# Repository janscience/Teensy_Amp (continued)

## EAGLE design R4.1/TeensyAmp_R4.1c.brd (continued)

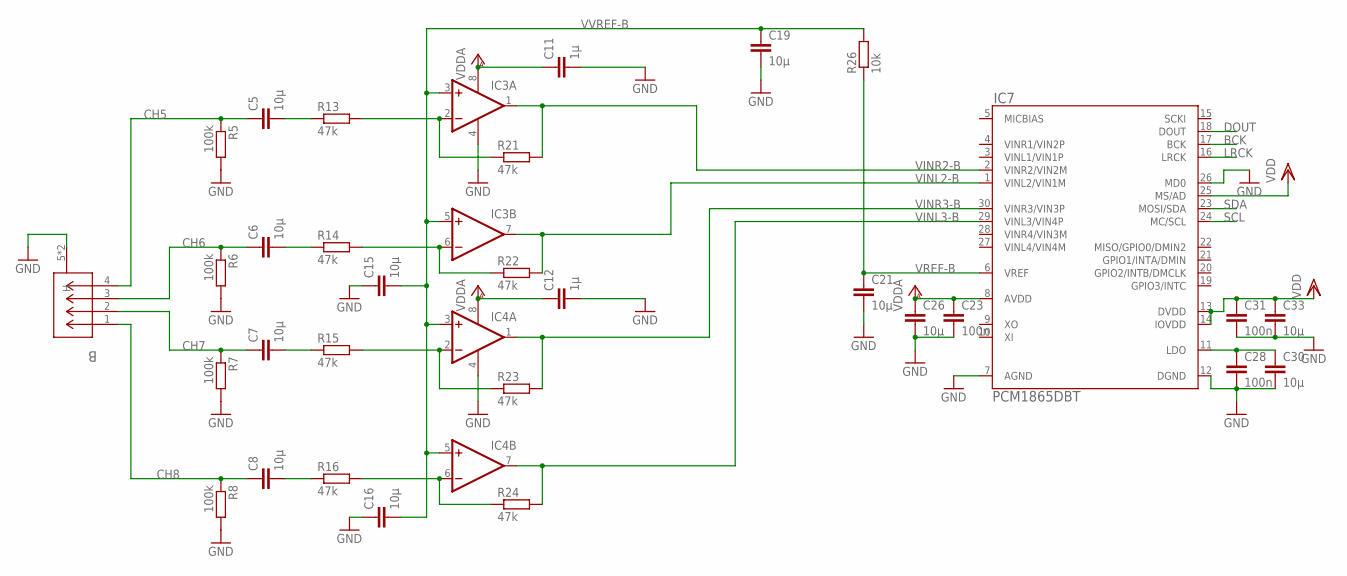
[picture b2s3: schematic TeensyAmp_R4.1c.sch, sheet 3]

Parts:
B: 5055670471; CONN04_5055670471_MOL
C5, C6, C7, C8: 10µ; C0805
C11, C12: 1µ; C0603
C15, C16, C19, C21, C26, C30, C33: 10µ; C0603
C23, C28, C31: 100n; C0603
IC3, IC4: OPA2344E; MSOP08
IC7: PCM1865DBT; SOP50P640X120-30N
R5, R6, R7, R8: 100k; R0603
R13, R14, R15, R16, R21, R22, R23, R24: 47k; R0603
R26: 10k; R0603

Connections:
BCK: IC7.17 (BCK); also elsewhere on the board
CH5: B.4, C5.1, R5.1
CH6: B.3, C6.1, R6.1
CH7: B.2, C7.1, R7.1
CH8: B.1, C8.1, R8.1
DOUT: IC7.18 (DOUT); also elsewhere on the board
GND: B.5 (H), B.6 (H), C11.2, C12.2, C15.1, C16.1, C19.2, C21.2, C23.2, C26.2, C28.2, C30.2, C31.2, C33.2, IC3.4 (V-), IC4.4 (V-), IC7.7 (AGND), IC7.12 (DGND), IC7.26 (MD0), R5.2, R6.2, R7.2, R8.2; also elsewhere on the board
LRCK: IC7.16 (LRCK); also elsewhere on the board
unnamed: C28.1, C30.1, IC7.11 (LDO)
unnamed: IC3.2 (-IN), R13.2, R21.1
unnamed: IC3.6 (-IN), R14.2, R22.1
unnamed: IC4.2 (-IN), R15.2, R23.1
unnamed: IC4.6 (-IN), R16.2, R24.1
unnamed: C6.2, R14.1
unnamed: C7.2, R15.1
unnamed: C8.2, R16.1
unnamed: C5.2, R13.1
SCL: IC7.24 (MC/SCL); also elsewhere on the board
SDA: IC7.23 (MOSI/SDA); also elsewhere on the board
VDD: C31.1, C33.1, IC7.13 (DVDD), IC7.14 (IOVDD), IC7.25 (MS/AD); also elsewhere on the board
VDDA: C11.1, C12.1, C23.1, C26.1, IC3.8 (V+), IC4.8 (V+), IC7.8 (AVDD); also elsewhere on the board
VINL2-B: IC3.7 (OUT), IC7.1 (VINL2/VIN1M), R22.2
VINL3-B: IC4.7 (OUT), IC7.29 (VINL3/VIN4P), R24.2
VINR2-B: IC3.1 (OUT), IC7.2 (VINR2/VIN2M), R21.2
VINR3-B: IC4.1 (OUT), IC7.30 (VINR3/VIN3P), R23.2
VREF-B: C21.1, IC7.6 (VREF), R26.1
VVREF-B: C15.2, C16.2, C19.1, IC3.3 (+IN), IC3.5 (+IN), IC4.3 (+IN), IC4.5 (+IN), R26.2

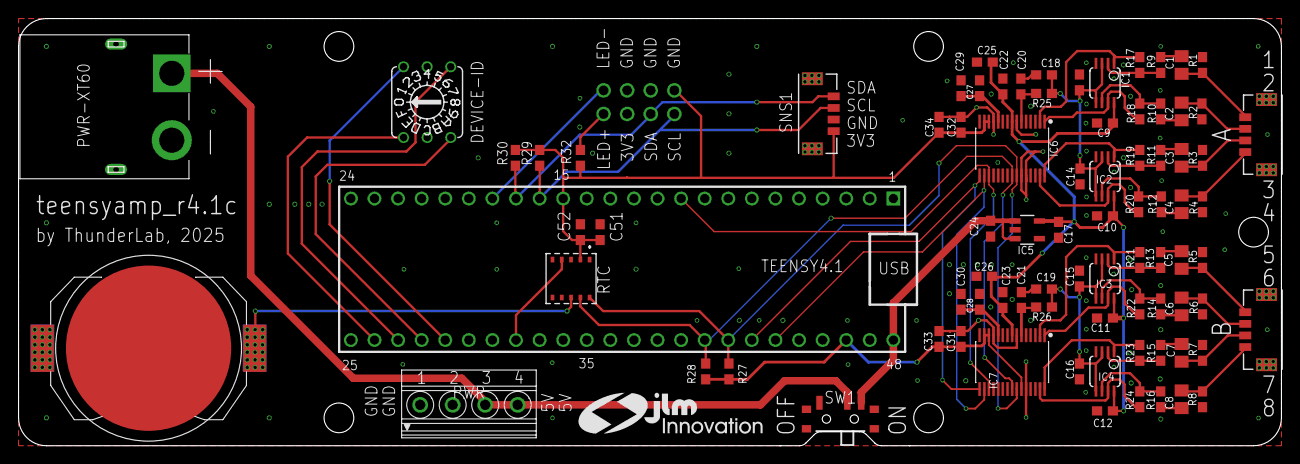
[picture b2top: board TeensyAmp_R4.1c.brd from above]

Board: 2 copper layers, 136.0 x 46.0 mm, 86 parts (0 on the bottom side), 58 nets.

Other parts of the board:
U$1: JLM_LOGO_MID

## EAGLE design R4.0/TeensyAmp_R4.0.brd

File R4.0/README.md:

# TeensyAmp R4.0

Based on
- 2 [TI PCM1865](pcm1865.md) with ADC and adjustable gain,
- [TI OPA1662](opa1662.pdf) as inverting pre-amplifier,
- [TI TCAN330](tcan334.pdf) CAN transceiver for synchronization.

by [jlm Innovation](https://www.jlm-innovation.de/) and [Jan
Benda](https://github.com/janscience).

## Circuit

- [EAGLE schematics file](TeensyAmp_R4.0.sch)
- [EAGLE circuit board](TeensyAmp_R4.0.brd)

## Pins

| Teensy 4.1 pin |              |
| -------------: | :----------- |
| Vin            | Vin          |
| GND            | GND          |
| 3.3V           | IOVDD        |
| 18             | I2C SDA      |
| 19             | I2C SCL      |
| 21             | BCK          |
| 20             | LRCK         |
| 8              | DOUT         |
| 28             | GPIO2 chip1  |
| 35             | GPIO2 chip2  |
| 29             | GPIO1 chip1  |
| 36             | GPIO1 chip2  |
| 6              | GPIO0 chip1  |
| 32             | GPIO0 chip2  |
| 0              | CAN RX       |
| 1              | CAN TX       |
| 24             | I/O In       |
| 25             | I/O Out      |
| 30             | Push button  |
| 31             | LED inverted |

### 8 input channels

The two [TI PCM1865](https://www.ti.com/product/PCM1865) together
provide 8 input channels.

You can choose between input channel that are attached to a
pre-amplifier with gain x10, or input channels without pre-amplifier
that receive the input directly via a passive high- and low-pass
filter.

| channel | PCM1865 pins with pre-amplifier | PCM1865 pins without pre-amplifier |
| ------: | :------------------------------ | :--------------------------------- |
| 0       | 1-CH1R                          | 1-CH3R                             |
| 1       | 1-CH1L                          | 1-CH3L                             |
| 2       | 1-CH2R                          | 1-CH4R                             |
| 3       | 1-CH2L                          | 1-CH4L                             |
| 4       | 2-CH1R                          | 2-CH3R                             |
| 5       | 2-CH1L                          | 2-CH3L                             |
| 6       | 2-CH2R                          | 2-CH4R                             |
| 7       | 2-CH2L                          | 2-CH4L                             |

In the following plot a 1kHz signal was supplied to each input channel in turn:

### Pre-amplifier

Inspired by
- http://realhdaudio.de/wp-content/uploads/2018/12/A0_HSD_TMT2018_realHDaudio_V3.pdf
- https://www.akm.com/content/dam/documents/products/audio/audio-adc/ak5397eq/ak5397eq-en-datasheet.pdf
- Figure 61 of the [PCM186x data sheet](https://www.ti.com/lit/gpn/pcm1865).

For variants of the pre-amplifier see [Testing filter and gain
variants](variants1.md) and [Testing high-pass filter without
low-pass](variants2.md).

#### Noise

All input channels short-circuited to ground.

- 0dB gain:

- 20dB gain:

- 40dB gain:

- No SD write artifacts.
- Super low 1-bit noise at 0dB gain.
- Noise increases accordingly with gain of the PCM chip.

#### Linearity

For the spectra, the sinewave stimuli have been applied to each
channel individually.

- 0dB gain, 150mV or 70mV rms sine wave:

- 20dB gain, 7mV rms sine wave:

- 40dB gain, 700uV rms sine wave:

- In all conditions harmonics are about 100dB below the signal!
- Noise increases according to gain (every x10 by 20dB).

#### Filter

Frequencies 10Hz to 20kHz in 1/3 octaves, each for 500ms on channel 0:

- 5Hz highpass filter

### Signal-filter (without pre-amplifier)

See figure 61 of the [PCM186x data sheet](https://www.ti.com/lit/gpn/pcm1865).

For variants of the signal filter see [Testing filter and gain
variants](variants1.md) and [Testing high-pass filter without
low-pass](variants2.md).

### Reference voltage

## CAN bus

You need to terminate both ends with a 120Ohm resistance.

## Power consumption

Teensy 4.1 on R4.0 board:

| V    | rate  | CPU    | I     | P    |
| ---- | ----- | ------ | ----- | ---- |
| 5V   | 96kHz | 600MHz | 300mA | 1.5W |
| 5V   | 96kHz | 450MHz | 270mA | 1.3W |
| 5V   | 96kHz | 150MHz | 240mA | 1.2W |
| 5V   | 96kHz |  24MHz |       |      |
| 5V   | 48kHz | 600MHz | 280mA | 1.4W |
| 5V   | 48kHz | 450MHz | 260mA | 1.3W |
| 5V   | 48kHz | 150MHz | 220mA | 1.1W |
| 5V   | 48kHz |  24MHz |       |      |
| 3.7V | 96kHz | 600MHz | 300mA | 1.1W |
| 3.7V | 96kHz | 450MHz | 270mA | 1.0W |
| 3.7V | 96kHz | 150MHz | 240mA | 0.9W |
| 3.7V | 96kHz |  24MHz |       |      |
| 3.7V | 48kHz | 600MHz | 280mA | 1.0W |
| 3.7V | 48kHz | 450MHz | 260mA | 0.9W |
| 3.7V | 48kHz | 150MHz | 220mA | 0.8W |
| 3.7V | 48kHz |  24MHz |       |      |

Underclocking works! But power savings are small.

Teensy 4.1 *without* R4.0 board:

| V    | rate  | CPU    | I     | P    |
| ---- | ----- | ------ | ----- | ---- |
| 5V   | 96kHz | 600MHz | 180mA | 0.9W |
| 5V   | 48kHz | 600MHz | 180mA | 0.9W |
| 5V   | 96kHz | 150MHz | 120mA | 0.6W |
| 5V   | 48kHz | 150MHz | 120mA | 0.6W |

The R4.0 board draws about 100mA of power.

## Battery life times

8 channel variant assumes 220mA consumption of Teensy and R4.0 amplifier board.

64 channel variant assumes 2A consumption (8x220mA consumption of Teensy and R4.0 amplifier board plus 240mA of control Teensy).

Power banks (5V):

| Capacity | 8 channels | 64 channels |
| -------- | ---------- | ----------- |
|  5Ah     |        22h |          2h |
| 10Ah     |        45h |          5h |
| 20Ah     |        90h |         10h |

Car battery (12V):

| Capacity | 8 channels | 64 channels |
| -------- | ---------- | ----------- |
| 10Ah     |       109h |         12h |
| 20Ah     |       218h |         24h |
| 40Ah     |       436h |         48h |

## Storage

For selecting appropriate SD cards, depending on sampling rates and
channels, see [data
rates](https://github.com/janscience/TeeRec/blob/main/docs/datarates.md).

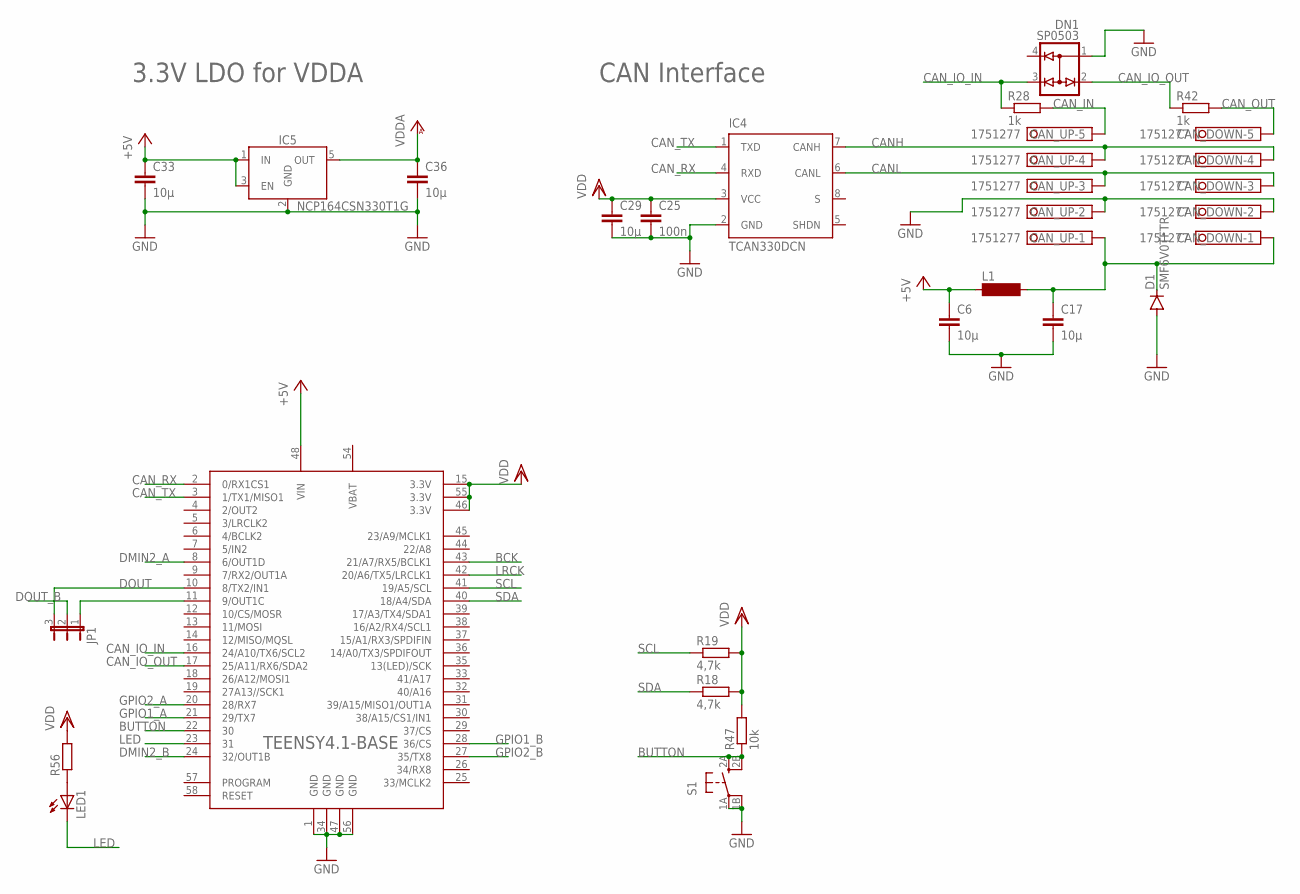
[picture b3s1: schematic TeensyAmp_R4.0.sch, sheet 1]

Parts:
C6, C17: 10µ; C0805
C25: 100n; 0402-N
C29, C33, C36: 10µ; C0603
CAN_DOWN: 1751277
CAN_UP: 1751277
D1: SMF6V0TFTR; SOD123
DN1: SP0503; SOT143-R
IC4: TCAN330DCN; SOT65P280X145-8N
IC5: NCP164CSN330T1G; SOT23-5
JP1: JP2E; JP2
L1: L_JLM0805; R0805
LED1: LEDCHIP-LED0603; CHIP-LED0603
R18, R19: 4,7k; R0402
R28, R42: 1k; 0402-N
R47: 10k; R0402
R56: R_JLMR0402; R0402
S1: SWITCH7914; 7914J
TEENSY4.1: TEENSY4.1

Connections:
+5V: C6.1, C33.1, IC5.1 (IN), IC5.3 (EN), L1.1, TEENSY4.1.48 (VIN)
BCK: TEENSY4.1.43 (21/A7/RX5/BCLK1); also elsewhere on the board
BUTTON: R47.1, S1.2A (S), S1.2B (S1), TEENSY4.1.22 (30)
CANH: CAN_DOWN.4, CAN_UP.4, IC4.7 (CANH)
CANL: CAN_DOWN.3, CAN_UP.3, IC4.6 (CANL)
CAN_IN: CAN_UP.5, R28.2
CAN_IO_IN: DN1.3 (C3), R28.1, TEENSY4.1.16 (24/A10/TX6/SCL2)
CAN_IO_OUT: DN1.2 (C2), R42.1, TEENSY4.1.17 (25/A11/RX6/SDA2)
CAN_OUT: CAN_DOWN.5, R42.2
CAN_RX: IC4.4 (RXD), TEENSY4.1.2 (0/RX1CS1)
CAN_TX: IC4.1 (TXD), TEENSY4.1.3 (1/TX1/MISO1)
DMIN2_A: TEENSY4.1.8 (6/OUT1D); also elsewhere on the board
DMIN2_B: TEENSY4.1.24 (32/OUT1B); also elsewhere on the board
DOUT: JP1.3, TEENSY4.1.10 (8/TX2/IN1); also elsewhere on the board
DOUT_B: JP1.2; also elsewhere on the board
GND: C6.2, C17.2, C25.2, C29.2, C33.2, C36.2, CAN_DOWN.2, CAN_UP.2, D1.A, DN1.1 (A1), IC4.2 (GND), IC5.2 (GND), S1.1A, S1.1B (P1), TEENSY4.1.1 (GND), TEENSY4.1.34 (GND), TEENSY4.1.47 (GND), TEENSY4.1.56 (GND); also elsewhere on the board
GPIO1_A: TEENSY4.1.21 (29/TX7); also elsewhere on the board
GPIO1_B: TEENSY4.1.28 (36/CS); also elsewhere on the board
GPIO2_A: TEENSY4.1.20 (28/RX7); also elsewhere on the board
GPIO2_B: TEENSY4.1.27 (35/TX8); also elsewhere on the board
LED: LED1.C, TEENSY4.1.23 (31)
LRCK: TEENSY4.1.42 (20/A6/TX5/LRCLK1); also elsewhere on the board
unnamed: C17.1, CAN_DOWN.1, CAN_UP.1, D1.C, L1.2
unnamed: LED1.A, R56.1
unnamed: JP1.1, TEENSY4.1.11 (9/OUT1C)
SCL: R19.1, TEENSY4.1.41 (19/A5/SCL); also elsewhere on the board
SDA: R18.1, TEENSY4.1.40 (18/A4/SDA); also elsewhere on the board
VBAT: TEENSY4.1.54 (VBAT)
VDD: C25.1, C29.1, IC4.3 (VCC), R18.2, R19.2, R47.2, R56.2, TEENSY4.1.15 (3.3V), TEENSY4.1.46 (3.3V), TEENSY4.1.55 (3.3V); also elsewhere on the board
VDDA: C36.1, IC5.5 (OUT); also elsewhere on the board

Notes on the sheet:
CAN Interface
3.3V LDO for VDDA

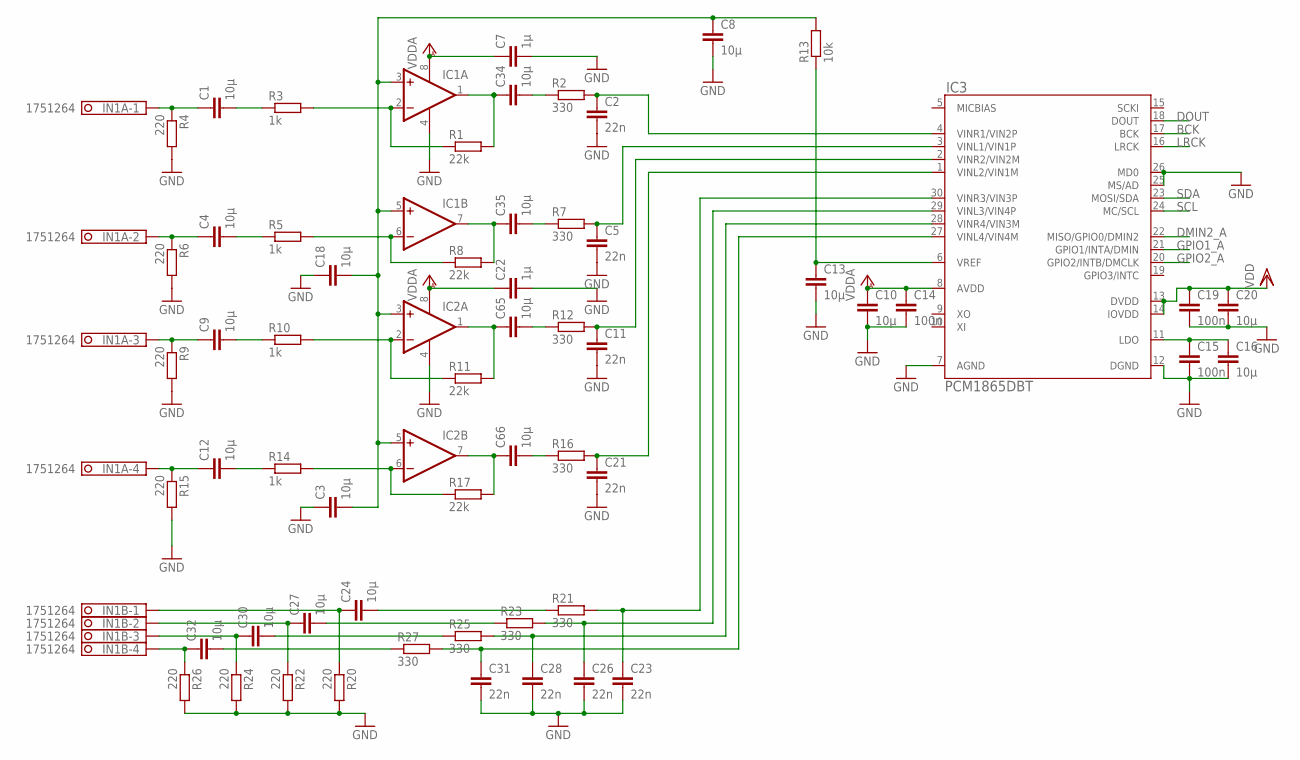
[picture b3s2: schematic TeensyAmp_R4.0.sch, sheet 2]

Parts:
C1, C4, C9, C12, C24, C27, C30, C32, C34, C35, C65, C66: 10µ; C0805
C2, C5, C11, C21, C23, C26, C28, C31: 22n; C0603
C3, C8, C10, C13, C16, C18, C20: 10µ; C0603
C7, C22: 1µ; C0603
C14, C15, C19: 100n; 0402-N
IC1, IC2: OPA2344E; MSOP08
IC3: PCM1865DBT; SOP50P640X120-30N
IN1A, IN1B: 1751264
R1, R8, R11, R17: 22k; R0603
R2, R7, R12, R16, R21, R23, R25, R27: 330; R0603
R3, R5, R10, R14: 1k; R0603
R4, R6, R9, R15, R20, R22, R24, R26: 220; R0603
R13: 10k; 0402-N

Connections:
BCK: IC3.17 (BCK); also elsewhere on the board
DMIN2_A: IC3.22 (MISO/GPIO0/DMIN2); also elsewhere on the board
DOUT: IC3.18 (DOUT); also elsewhere on the board
GND: C2.2, C3.1, C5.2, C7.2, C8.2, C10.2, C11.2, C13.2, C14.2, C15.2, C16.2, C18.1, C19.2, C20.2, C21.2, C22.2, C23.2, C26.2, C28.2, C31.2, IC1.4 (V-), IC2.4 (V-), IC3.7 (AGND), IC3.12 (DGND), IC3.25 (MS/AD), IC3.26 (MD0), R4.2, R6.2, R9.2, R15.2, R20.2, R22.2, R24.2, R26.2; also elsewhere on the board
GPIO1_A: IC3.21 (GPIO1/INTA/DMIN); also elsewhere on the board
GPIO2_A: IC3.20 (GPIO2/INTB/DMCLK); also elsewhere on the board
LRCK: IC3.16 (LRCK); also elsewhere on the board
unnamed: C31.1, IC3.27 (VINL4/VIN4M), R27.2
unnamed: C28.1, IC3.28 (VINR4/VIN3M), R25.2
unnamed: C26.1, IC3.29 (VINL3/VIN4P), R23.2
unnamed: C23.1, IC3.30 (VINR3/VIN3P), R21.2
unnamed: C21.1, IC3.1 (VINL2/VIN1M), R16.2
unnamed: C11.1, IC3.2 (VINR2/VIN2M), R12.2
unnamed: C5.1, IC3.3 (VINL1/VIN1P), R7.2
unnamed: C2.1, IC3.4 (VINR1/VIN2P), R2.2
unnamed: C32.2, R27.1
unnamed: C24.1, IN1B.1, R20.1
unnamed: C15.1, C16.1, IC3.11 (LDO)
unnamed: C27.1, IN1B.2, R22.1
unnamed: C30.1, IN1B.3, R24.1
unnamed: C32.1, IN1B.4, R26.1
unnamed: C12.1, IN1A.4, R15.1
unnamed: C9.1, IN1A.3, R9.1
unnamed: C4.1, IN1A.2, R6.1
unnamed: C30.2, R25.1
unnamed: C1.1, IN1A.1, R4.1
unnamed: C27.2, R23.1
unnamed: C4.2, R5.1
unnamed: C9.2, R10.1
unnamed: C1.2, R3.1
unnamed: C12.2, R14.1
unnamed: C34.1, IC1.1 (OUT), R1.2
unnamed: C35.1, IC1.7 (OUT), R8.2
unnamed: C65.1, IC2.1 (OUT), R11.2
unnamed: IC1.2 (-IN), R1.1, R3.2
unnamed: IC1.6 (-IN), R5.2, R8.1
unnamed: IC2.2 (-IN), R10.2, R11.1
unnamed: IC2.6 (-IN), R14.2, R17.1
unnamed: C66.1, IC2.7 (OUT), R17.2
unnamed: C24.2, R21.1
unnamed: C13.1, IC3.6 (VREF), R13.1
unnamed: C34.2, R2.1
unnamed: C3.2, C8.1, C18.2, IC1.3 (+IN), IC1.5 (+IN), IC2.3 (+IN), IC2.5 (+IN), R13.2
unnamed: C35.2, R7.1
unnamed: C65.2, R12.1
unnamed: C66.2, R16.1
SCL: IC3.24 (MC/SCL); also elsewhere on the board
SDA: IC3.23 (MOSI/SDA); also elsewhere on the board
VDD: C19.1, C20.1, IC3.13 (DVDD), IC3.14 (IOVDD); also elsewhere on the board
VDDA: C7.1, C10.1, C14.1, C22.1, IC1.8 (V+), IC2.8 (V+), IC3.8 (AVDD); also elsewhere on the board

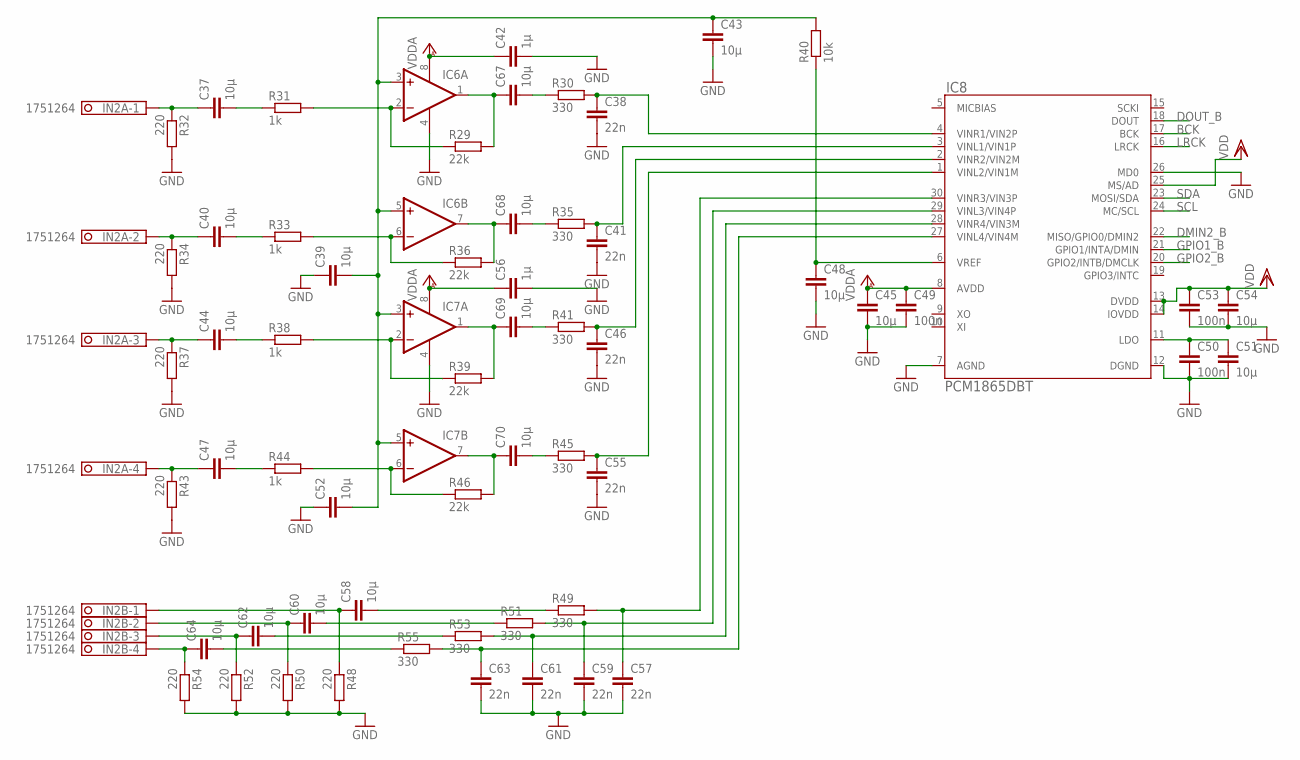
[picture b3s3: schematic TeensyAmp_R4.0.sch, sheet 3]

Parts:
C37, C40, C44, C47, C58, C60, C62, C64, C67, C68, C69, C70: 10µ; C0805
C38, C41, C46, C55, C57, C59, C61, C63: 22n; C0603
C39, C43, C45, C48, C51, C52, C54: 10µ; C0603
C42, C56: 1µ; C0603
C49, C50, C53: 100n; 0402-N
IC6, IC7: OPA2344E; MSOP08
IC8: PCM1865DBT; SOP50P640X120-30N
IN2A, IN2B: 1751264
R29, R36, R39, R46: 22k; R0603
R30, R35, R41, R45, R49, R51, R53, R55: 330; R0603
R31, R33, R38, R44: 1k; R0603
R32, R34, R37, R43, R48, R50, R52, R54: 220; R0603
R40: 10k; 0402-N

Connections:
BCK: IC8.17 (BCK); also elsewhere on the board
DMIN2_B: IC8.22 (MISO/GPIO0/DMIN2); also elsewhere on the board
DOUT_B: IC8.18 (DOUT); also elsewhere on the board
GND: C38.2, C39.1, C41.2, C42.2, C43.2, C45.2, C46.2, C48.2, C49.2, C50.2, C51.2, C52.1, C53.2, C54.2, C55.2, C56.2, C57.2, C59.2, C61.2, C63.2, IC6.4 (V-), IC7.4 (V-), IC8.7 (AGND), IC8.12 (DGND), IC8.26 (MD0), R32.2, R34.2, R37.2, R43.2, R48.2, R50.2, R52.2, R54.2; also elsewhere on the board
GPIO1_B: IC8.21 (GPIO1/INTA/DMIN); also elsewhere on the board
GPIO2_B: IC8.20 (GPIO2/INTB/DMCLK); also elsewhere on the board
LRCK: IC8.16 (LRCK); also elsewhere on the board
unnamed: C63.1, IC8.27 (VINL4/VIN4M), R55.2
unnamed: C61.1, IC8.28 (VINR4/VIN3M), R53.2
unnamed: C59.1, IC8.29 (VINL3/VIN4P), R51.2
unnamed: C57.1, IC8.30 (VINR3/VIN3P), R49.2
unnamed: C55.1, IC8.1 (VINL2/VIN1M), R45.2
unnamed: C46.1, IC8.2 (VINR2/VIN2M), R41.2
unnamed: C41.1, IC8.3 (VINL1/VIN1P), R35.2
unnamed: C50.1, C51.1, IC8.11 (LDO)
unnamed: C58.1, IN2B.1, R48.1
unnamed: C60.1, IN2B.2, R50.1
unnamed: C62.1, IN2B.3, R52.1
unnamed: C64.1, IN2B.4, R54.1
unnamed: IC6.2 (-IN), R29.1, R31.2
unnamed: IC6.6 (-IN), R33.2, R36.1
unnamed: IC7.2 (-IN), R38.2, R39.1
unnamed: IC7.6 (-IN), R44.2, R46.1
unnamed: C40.2, R33.1
unnamed: C44.2, R38.1
unnamed: C47.2, R44.1
unnamed: C37.2, R31.1
unnamed: C47.1, IN2A.4, R43.1
unnamed: C44.1, IN2A.3, R37.1
unnamed: C40.1, IN2A.2, R34.1
unnamed: C37.1, IN2A.1, R32.1
unnamed: C38.1, IC8.4 (VINR1/VIN2P), R30.2
unnamed: C62.2, R53.1
unnamed: C60.2, R51.1
unnamed: C58.2, R49.1
unnamed: C64.2, R55.1
unnamed: C48.1, IC8.6 (VREF), R40.1
unnamed: C69.1, IC7.1 (OUT), R39.2
unnamed: C68.1, IC6.7 (OUT), R36.2
unnamed: C67.1, IC6.1 (OUT), R29.2
unnamed: C70.1, IC7.7 (OUT), R46.2
unnamed: C39.2, C43.1, C52.2, IC6.3 (+IN), IC6.5 (+IN), IC7.3 (+IN), IC7.5 (+IN), R40.2
unnamed: C70.2, R45.1
unnamed: C69.2, R41.1
unnamed: C68.2, R35.1
unnamed: C67.2, R30.1
SCL: IC8.24 (MC/SCL); also elsewhere on the board
SDA: IC8.23 (MOSI/SDA); also elsewhere on the board
VDD: C53.1, C54.1, IC8.13 (DVDD), IC8.14 (IOVDD), IC8.25 (MS/AD); also elsewhere on the board
VDDA: C42.1, C45.1, C49.1, C56.1, IC6.8 (V+), IC7.8 (V+), IC8.8 (AVDD); also elsewhere on the board

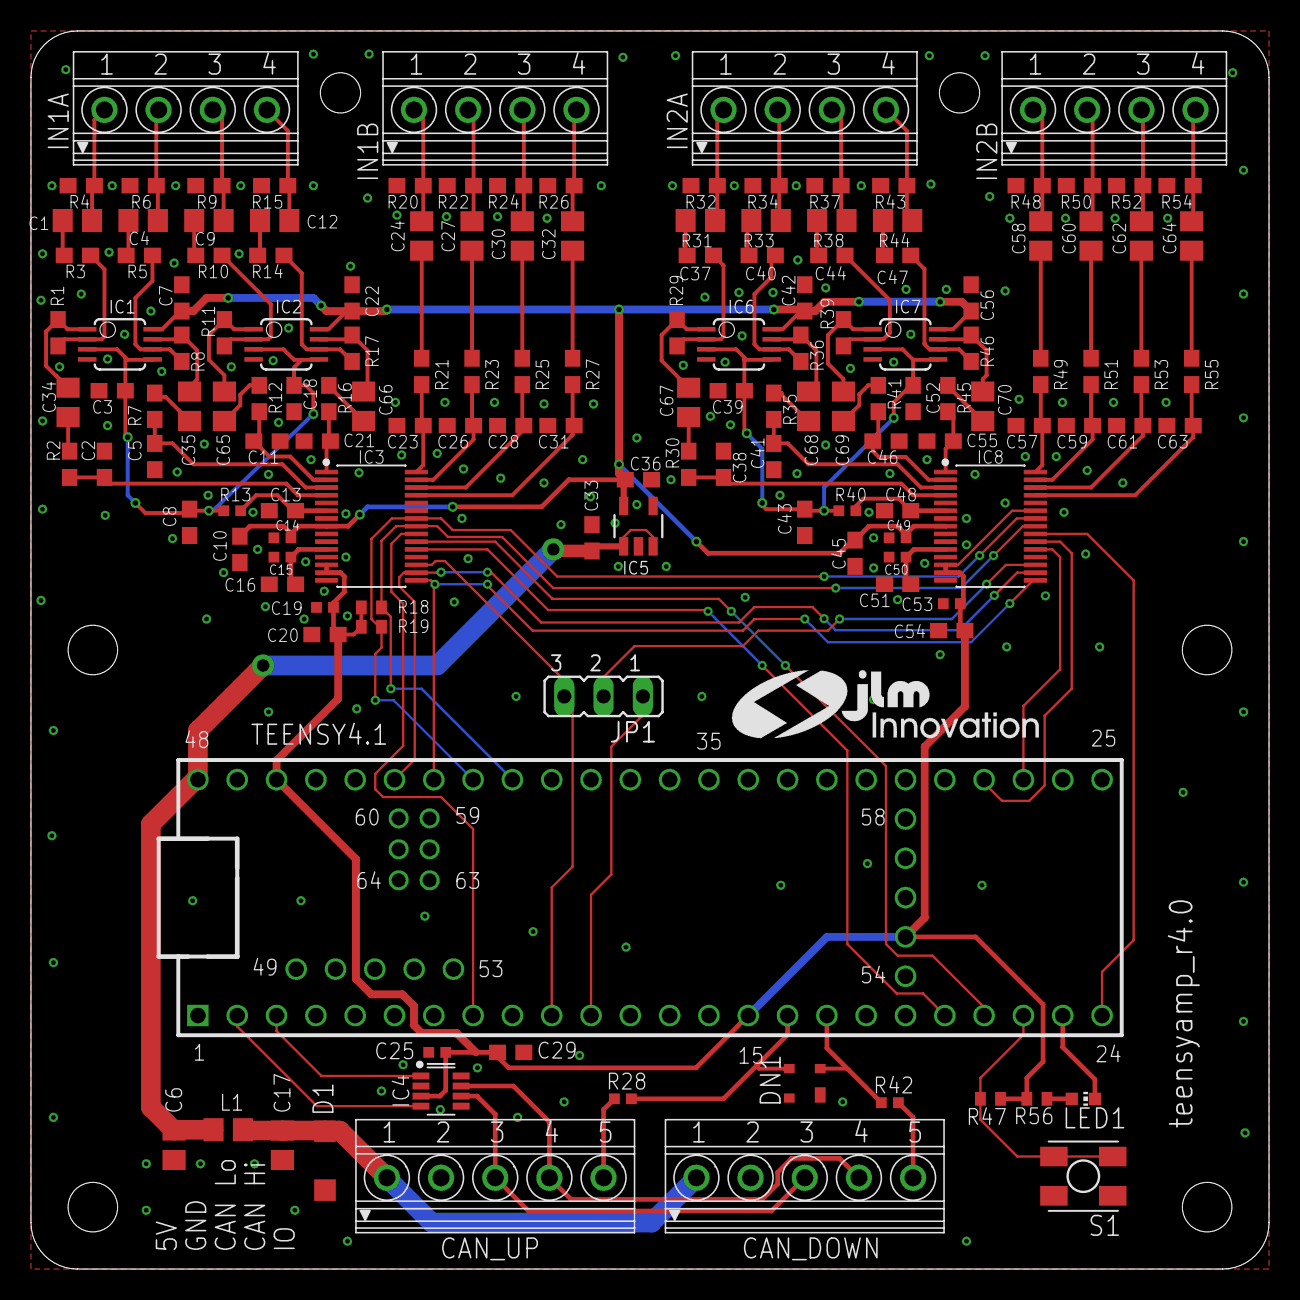
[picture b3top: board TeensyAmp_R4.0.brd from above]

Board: 2 copper layers, 80.0 x 80.0 mm, 148 parts (0 on the bottom side), 107 nets.

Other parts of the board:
U$1: JLM_LOGO_MID

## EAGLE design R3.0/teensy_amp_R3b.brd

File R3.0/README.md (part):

# TeensyAmp R3.0

by [jlm Innovation](https://www.jlm-innovation.de/) and [Jan
Benda](https://github.com/janscience), based on the R2.0 circuit by
[Stefan Mucha](https://github.com/muchaste).

The input signals are processed in the following way:

- simple RC high-pass filtering, cutoff frequencies selectable via
  plug-in capacitors.

- amplification ([Texas Instruments
  INA2321-EA](https://www.ti.com/product/INA2321)),
  gain selectable via plug-in resistances.

- low-pass filtering ([Analog devices
  OP2177ARZ](https://www.analog.com/media/en/technical-documentation/data-sheets/op1177_2177_4177.pdf)),
  cutoff frequencies selectable via plug-in resistances.

- An [Onsemi
  NCP164ASN330](https://www.onsemi.jp/products/power-management/linear-regulators-ldo/ncp164?pdf=Y)
  generates the 3.3V for power and analog reference.

- An LDO, [Analog Devices
  ADR3412](https://www.analog.com/en/products/adr3412.html),
  generatesd the 1.6V reference.

## Circuit

- [EAGLE schematics file](teensy_amp_R3b.sch)
- [EAGLE circuit board](teensy_amp_R3b.brd)

## Pins

Note:
- RTP1, RGAIN1, CHP1A, CHP1B are for channel 2
- RTP2, RGAIN2, CHP2A, CHP2B are for channel 1

### Input

The signal to be measured is connected via the screw-terminal block on
the right.

- The two inner pins are the positive V+ inputs.
- The two outer pins are the negative V- inputs.

### Output

Each of the amplified signals can be assinged to one of four analog
input pins of the Teensy. The following tables also indicate from
which of the two ADCs those pins can be accessed on a Teensy 3.5 or
3.6

Signal 1 (Channel1):

| Pad    | Teensy | ADC0 | ADC1 | Board |
| ------ | ------ | ---- | ---- | ----- |
| S1_A10 | A10    | 1    | 1    | A X   | 
| S1_A11 | A11    | 0    | 1    | B Y   | 
| S1_A7  | A7     | 1    | 0    | C     | 
| S1_A6  | A6     | 1    | 0    | D     | 

Signal 2 (Channel2):

| Pad    | Teensy | ADC0 | ADC1 | Board |
| ------ | ------ | ---- | ---- | ----- |
| S2_A5  | A5     | 1    | 0    | A     |  
| S2_A4  | A4     | 1    | 0    | B     |  
| S2_A3  | A3     | 1    | 1    | C Y   |  
| S2_A2  | A2     | 1    | 1    | D X   |  

### Power

- Vin: 3.3V - 5V on bottom left pin (Teensy Vin).
- GND: on top left pin (Teensy GND).

## Gain

Gain of the INA is given by

where *R1 = RGAIN1* and *R2* = *R9* = 100kOhm.

The total gain of the amplifier is the INA gain times 1.7.

| RGAIN1  | INA gain  | Total gain |
| ------: | --------: | ---------: |
|   1MOhm |       5.5 |            |
| 100kOhm |        10 |            |
|  47kOhm |        15 |            |
|  27kOhm |        24 |         40 |
|  12kOhm |        47 |         80 |
|  10kOhm |        55 |            |
| 5.6kOhm |        94 |        160 |
| 4.7kOhm |       111 |            |
| 2.2kOhm |       232 |        400 |
| 1.5kOhm |       338 |            |
|   1kOhm |       505 |        870 |
|  500Ohm |      1005 |            |
|  200Ohm |      2505 |            |
|  100Ohm |      5005 |            |
|   50Ohm |     10005 |            |

## Filter

### High-pass filter

| R1-R4   | CHP1A-CHP2B | tau    | fcutoff | real fcutoff |
| ------: | ----------: | -----: | ------: | -----------: |
| 100kOhm | 220nF       | 22ms   |   7.2Hz |        <10Hz |
| 100kOhm | 150nF       | 15ms   |  10.6Hz |              |
| 100kOhm |  22nF       | 2.2ms  |  72Hz   |         70Hz |
| 100kOhm |  15nF       | 1.5ms  | 106Hz   |              |
| 100kOhm | 5.6nF       | 0.56ms | 283Hz   |              |
| 100kOhm | 4.7nF       | 0.47ms | 338Hz   |              |

### Low-pass filter

*C* = 820pF
*R* = RTP1 + 4.5kOhm

| RTP1, RTP2 | fcutoff | sampling rate | real fcutoff |
| ---------: | ------: | ------------: | -----------: |
|  27kOhm    |  7kHz   |  20kHz        |         8kHz |
|  12kOhm    | 15kHz   |  44kHz        |        15kHz |
| 5.6kOhm    | 20kHz   |  60kHz        |              |
| 2.2kOhm    | 29kHz   |  87kHz        |       >20kHz |
| 1.5kOhm    | 33kHz   | 100kHz        |              |
|   1kOhm    | 35kHz   | 106kHz        |              |

## Gain and linearity tests

### Control

Sine wave recorded with Measurement Computing USB_1608_GX_2AO:

The sine wave generator (NTI Minirator) produces a third harmonic
ca. 70dB below fundamental. Very clean sine wave!

### Gain tests

In files [`tests/gain-*.wav`](tests) sine wave signals were recorded
with various gains (70Hz high-pass, 7kHz low-pass).

x40: RGAIN1=27kOhm with 20mV rms amplitude (56mV p-p):

x80: RGAIN1=12kOhm with 10mV rms amplitude (28mV p-p):

x160: RGAIN1=5.6kOhm with 5mV rms amplitude (14mV p-p):

x400: RGAIN1=2.2kOhm with 2mV rms amplitude (5.6mV p-p):

x800: RGAIN1=1kOhm with 1mV rms amplitude (2.8mV p-p):

### Conclusion

- Amplifier and/or Teensy produce many harmonics. And they are only
  about 25dB below the fundamental.
- Noisy at gains larger x100.

## Transfer function and filter tests

In files [`tests/filter-*.wav`](tests) a 20mV rms signal was sampled with
44kHz and its frequency was increased as follows: 10Hz, 12.5Hz, 16Hz,
20Hz, 25Hz, 31.5Hz, 40Hz, 50Hz, 63Hz, 80Hz, 100Hz, 125Hz, 160Hz,
200Hz, 250Hz, 315Hz, 400Hz, 500Hz, 630Hz, 800Hz, 1000Hz, 1250Hz,
1600Hz, 2000Hz, 2500Hz, 3150Hz, 4000Hz, 5000Hz, 6300Hz, 8000Hz,
10kHz, 12.5kHz, 16kHz, 20kHz.

7Hz high-pass, 7kHz low-pass:

70Hz high-pass, 7kHz low-pass:

70Hz high-pass, 15kHz low-pass:

70Hz high-pass, 29kHz low-pass:

### Conclusion

- High- and low-pass filter are working as expected.
- Pass-band should be flatter.

## Signal range and clipping

### Conclusion

- The full output voltage range is used.

## Noise and SD write artifacts

### AREF configuration

Gain 27kOhm, HF 22nF, LW 27kOhm:

- Plain amplifier output recorded with Measurement Computing
  USB_1608_GX_2AO (range 1V):

- Teensy internal 3.3V REF:

- Amplifier LDO 3.3V connected to AREF:

- Amplifier LDO 3.3V connected to AREF, AGND connected to GND:

### Gain dependence

Amplifier LDO 3.3V connected to AREF, HF 220nF, LW 27kOhm.
  
- Gain 12kOhm:

- Gain 5.6kOhm:

- Gain 2.2kOhm:

- Gain 1kOhm:

- Gain 1kOhm, AGND connected to GND:

### Conclusion

- The LDO of the amplifier seems to be able to produce a stable voltage from
  the supply voltage of the Teensy:
  Amplified short circuited signals are stable and do not show SD
  write artifacts.
- Using the Teensy's ADC however shows the SD write artifacts.
- SD write artifact gets smaller when AREF is driven by LDO voltage.
- Removing Teensy's R3 resistance does not make a difference
  (see `../images/sdwrites-*noR3*`).
- Connecting AGND to GND does not make a difference.
- The larger the gain, the larger the baseline noise.

## ADC settings

For a gain of 40x (27kOhm), highpass filter of 70Hz (22nF), lowpass
filter of 7kHz (27kOhm) and a sampling rate of 20kHz, the [averaging
sketch](https://github.com/janscience/TeeRec/tree/main/examples/averaging)
reports (sampling rate of 100kHz gives similar results):

| convers  | sampling | avrg |   A2 |  A10 |
| :------- | :------- | ---: | ---: | ---: |
| veryhigh | veryhigh |    1 |  1.4 |  1.3 |
| veryhigh | veryhigh |    4 |  0.9 |  0.9 |
| veryhigh | veryhigh |    8 |  0.9 |  0.9 |
| veryhigh | veryhigh |   16 |  0.9 |  0.8 |
| veryhigh | veryhigh |   32 |  0.7 |  0.8 |
| veryhigh | high     |    1 |  1.2 |  1.1 |
| veryhigh | high     |    4 |  0.9 |  0.9 |
| veryhigh | high     |    8 |  0.8 |  0.9 |
| veryhigh | high     |   16 |  0.8 |  0.7 |
| veryhigh | high     |   32 |  0.9 |  0.9 |
| veryhigh | med      |    1 |  1.1 |  1.1 |
| veryhigh | med      |    4 |  0.9 |  0.8 |
| veryhigh | med      |    8 |  0.8 |  0.8 |
| veryhigh | med      |   16 |  0.8 |  0.8 |
| veryhigh | med      |   32 |  0.9 |  1.0 |
| veryhigh | low      |    1 |  1.2 |  1.2 |
| veryhigh | low      |    4 |  0.9 |  0.9 |
| veryhigh | low      |    8 |  0.7 |  0.8 |
| veryhigh | low      |   16 |  0.8 |  0.8 |
| veryhigh | low      |   32 |  0.8 |  0.7 |
| veryhigh | verylow  |    1 |  1.3 |  1.2 |
| veryhigh | verylow  |    4 |  0.8 |  0.9 |
| veryhigh | verylow  |    8 |  0.8 |  0.9 |
| veryhigh | verylow  |   16 |  0.8 |  0.8 |
| veryhigh | verylow  |   32 |  0.8 |  0.7 |
| high     | veryhigh |    1 |  1.1 |  1.4 |
| high     | veryhigh |    4 |  0.8 |  0.9 |
| high     | veryhigh |    8 |  0.8 |  1.0 |
| high     | veryhigh |   16 |  0.8 |  0.9 |
| high     | veryhigh |   32 |  0.7 |  0.7 |
| high     | high     |    1 |  1.1 |  1.2 |
| high     | high     |    4 |  0.9 |  1.0 |
| high     | high     |    8 |  0.9 |  0.9 |
| high     | high     |   16 |  0.8 |  0.7 |
| high     | med      |    1 |  1.1 |  1.1 |
| high     | med      |    4 |  0.9 |  0.8 |
| high     | med      |    8 |  0.8 |  0.8 |
| high     | med      |   16 |  0.8 |  0.8 |
| high     | low      |    1 |  1.1 |  1.0 |
| high     | low      |    4 |  0.9 |  0.8 |
| high     | low      |    8 |  0.8 |  0.8 |
| high     | low      |   16 |  0.8 |  0.7 |
| high     | verylow  |    1 |  1.1 |  1.0 |
| high     | verylow  |    4 |  0.8 |  0.8 |
| high     | verylow  |    8 |  0.8 |  0.8 |
| high     | verylow  |   16 |  0.7 |  0.7 |
| med      | veryhigh |    1 |  1.1 |  1.3 |
| med      | veryhigh |    4 |  0.9 |  0.8 |
| med      | veryhigh |    8 |  0.8 |  0.8 |
| med      | veryhigh |   16 |  0.7 |  0.8 |
| med      | high     |    1 |  1.1 |  1.0 |
| med      | high     |    4 |  0.8 |  0.8 |
| med      | high     |    8 |  0.8 |  0.8 |
| med      | high     |   16 |  0.7 |  0.7 |
| med      | med      |    1 |  1.2 |  1.1 |
| med      | med      |    4 |  0.8 |  0.8 |
| med      | med      |    8 |  0.9 |  0.8 |
| med      | low      |    1 |  1.2 |  1.0 |
| med      | low      |    4 |  0.8 |  0.8 |
| med      | low      |    8 |  0.8 |  0.7 |
| med      | verylow  |    1 |  1.2 |  1.3 |
| med      | verylow  |    4 |  0.9 |  0.9 |
| med      | verylow  |    8 |  0.7 |  0.7 |

A good setting:

With the same settings but with 16bit the results look like this:

| convers  | sampling | avrg |   A2 |  A10 |
| :------- | :------- | ---: | ---: | ---: |
| veryhigh | veryhigh |    1 | 17.4 | 15.7 |
| veryhigh | veryhigh |    4 | 15.1 | 12.7 |
| veryhigh | veryhigh |    8 | 12.5 | 11.4 |
| veryhigh | veryhigh |   16 | 12.3 | 11.7 |
| veryhigh | veryhigh |   32 | 14.9 | 11.0 |
| veryhigh | high     |    1 | 16.5 | 18.3 |
| veryhigh | high     |    4 | 12.8 | 10.8 |
| veryhigh | high     |    8 | 13.4 | 13.0 |
| veryhigh | high     |   16 | 11.8 | 11.4 |
| veryhigh | high     |   32 | 13.4 | 11.8 |
| veryhigh | med      |    1 | 15.7 | 15.3 |
| veryhigh | med      |    4 | 12.5 | 12.7 |
| veryhigh | med      |    8 | 12.3 | 12.2 |
| veryhigh | med      |   16 | 10.8 | 10.7 |
| veryhigh | med      |   32 | 10.5 | 11.5 |
| veryhigh | low      |    1 | 19.7 | 15.1 |
| veryhigh | low      |    4 | 11.7 |  9.1 |
| veryhigh | low      |    8 | 11.7 | 11.8 |
| veryhigh | low      |   16 | 11.8 | 11.5 |
| veryhigh | low      |   32 | 10.2 | 10.2 |
| veryhigh | verylow  |    1 | 17.5 | 15.5 |
| veryhigh | verylow  |    4 | 11.9 | 11.4 |
| veryhigh | verylow  |    8 | 11.4 | 11.2 |
| veryhigh | verylow  |   16 | 11.0 | 11.0 |
| high     | veryhigh |    1 | 16.6 | 14.2 |
| high     | veryhigh |    4 | 11.8 | 11.9 |
| high     | veryhigh |    8 | 11.2 | 11.3 |
| high     | veryhigh |   16 | 10.7 | 11.0 |
| high     | high     |    1 | 15.3 | 14.5 |
| high     | high     |    4 | 12.0 | 11.9 |
| high     | high     |    8 | 11.2 | 11.0 |
| high     | high     |   16 | 11.1 | 11.4 |
| high     | med      |    1 | 15.5 | 15.4 |
| high     | med      |    4 | 12.2 | 11.8 |
| high     | med      |    8 | 11.7 | 12.2 |
| high     | med      |   16 | 10.7 | 11.1 |
| high     | low      |    1 | 16.1 | 14.9 |
| high     | low      |    4 | 12.5 | 12.2 |
| high     | low      |    8 | 11.7 | 10.9 |
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
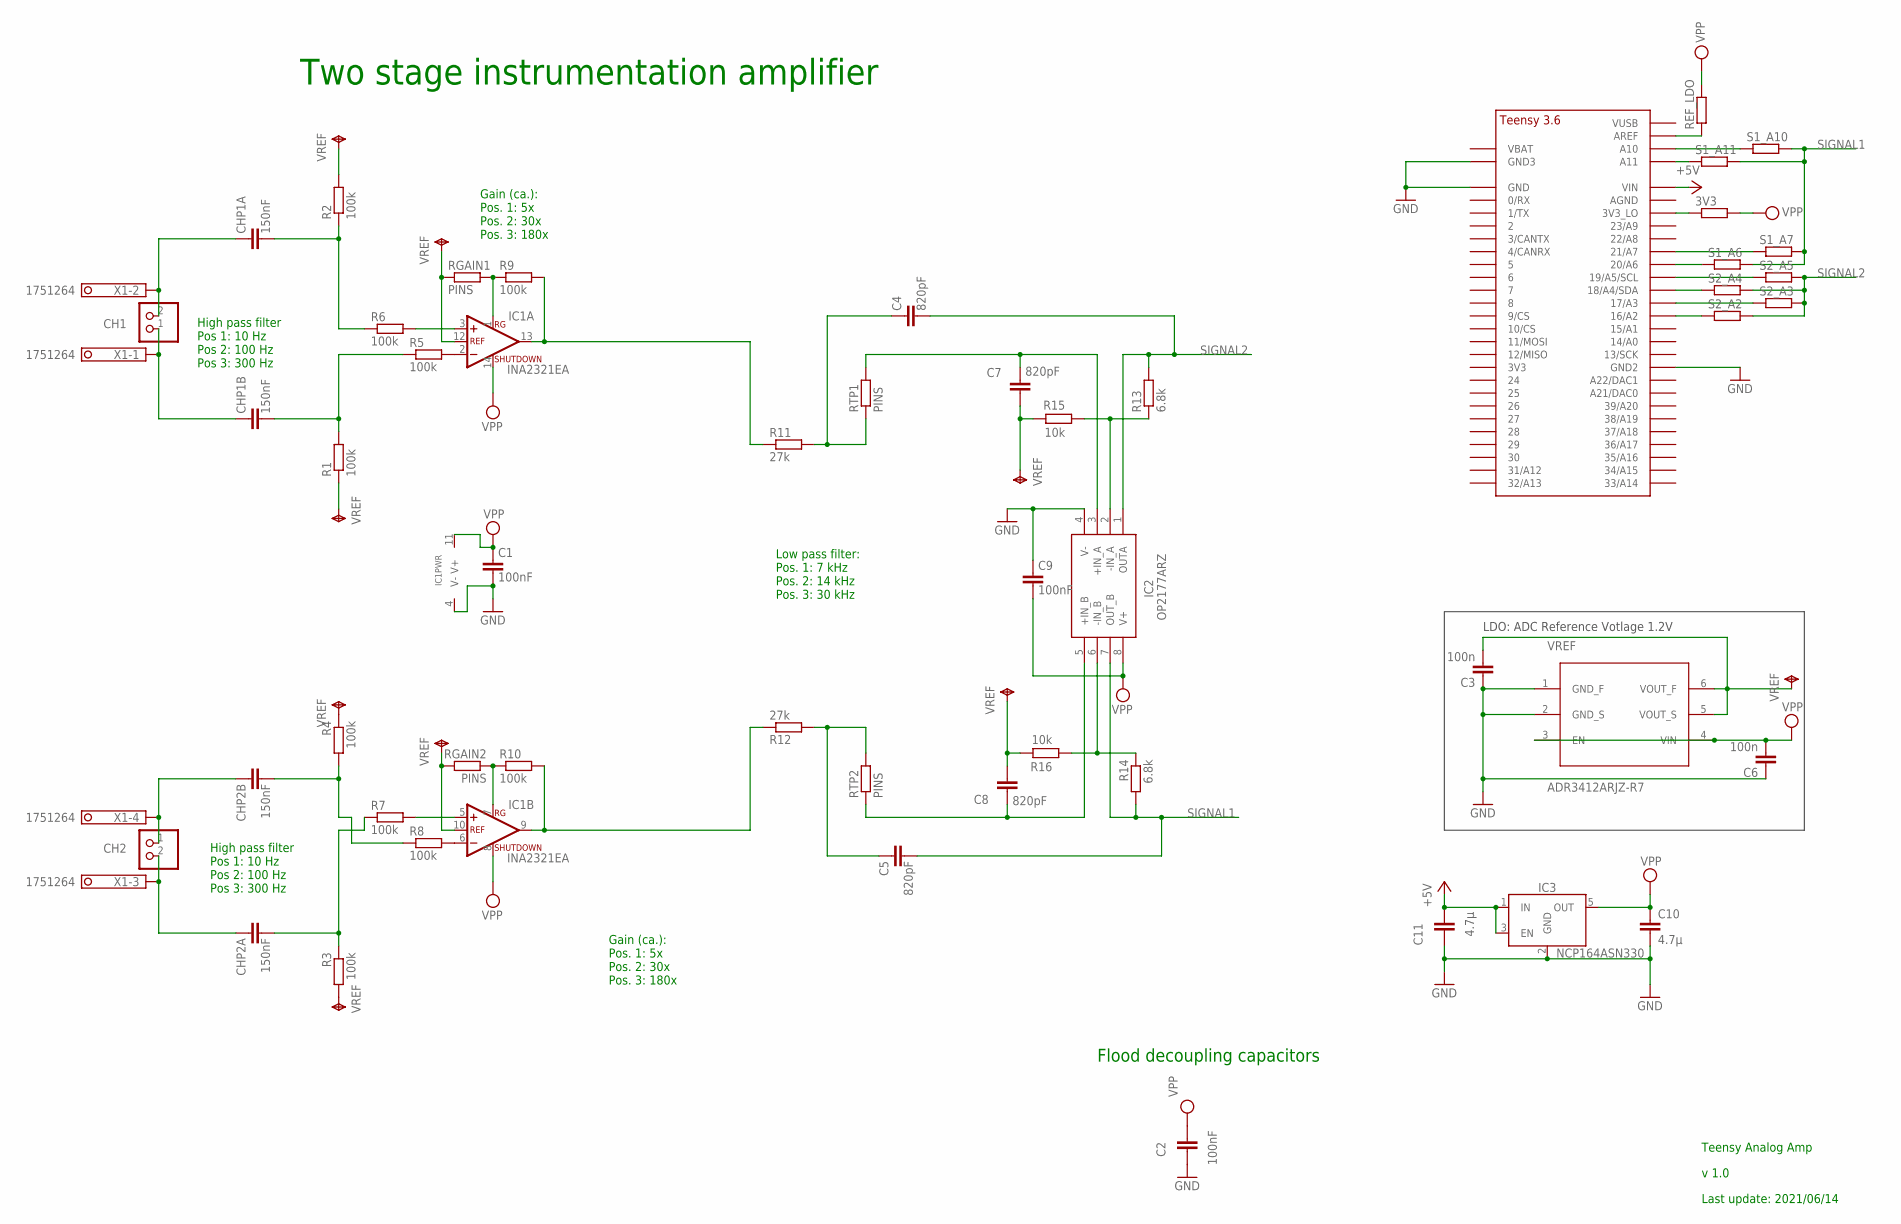
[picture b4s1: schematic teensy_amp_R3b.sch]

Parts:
3V3: R_JLM0402-NARROW; 0402-N
C1, C2, C9: 100nF; C0603
C3, C6: 100n; C0603
C4, C5, C7, C8: 820pF; C0603
C10, C11: 4.7µ; C0603
CH1, CH2: PINHD-1X2; 1X02
CHP1A, CHP1B, CHP2A, CHP2B: 150nF; C_PINS
IC1: INA2321EA; TSSOP14
IC2: OP2177ARZ; SOIC127P600X175-8N
IC3: NCP164ASN330; SOT23-5
R1, R2, R3, R4, R5, R6, R7, R8, R9, R10: 100k; R0603
R11, R12: 27k; R0603
R13, R14: 6.8k; R0603
R15, R16: 10k; R0603
REF_LDO: R_JLM0402-NARROW; 0402-N
RGAIN1, RGAIN2: PINS; R_PINS
RTP1, RTP2: PINS; R_PINS
S1_A6, S1_A7, S1_A10, S1_A11, S2_A2, S2_A3, S2_A4, S2_A5: R_JLM0402-NARROW; 0402-N
U$1: TEENSY_3.5/3.6_SOCKET_VBAT; TEENY_3.5/3.6_SOCKET_VBAT
VREF: ADR3412ARJZ-R7; SOT23-6
X1: 1751264

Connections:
+5V: C11.2, IC3.1 (IN), IC3.3 (EN), U$1.VIN
GND: C1.2, C2.1, C3.1, C6.1, C9.1, C10.2, C11.1, IC1.4 (V-), IC2.4 (V-), IC3.2 (GND), U$1.GND, U$1.GND2, U$1.GND3, VREF.1 (GND_F), VREF.2 (GND_S)
unnamed: CH1.2, CHP1A.1, X1.2
unnamed: CH1.1, CHP1B.1, X1.1
unnamed: C4.1, R11.2, RTP1.1
unnamed: IC1.2 (-IN), R5.2
unnamed: IC1.1 (RG), R9.1, RGAIN1.2
unnamed: IC1.3 (+IN), R6.2
unnamed: S1_A10.1, U$1.A10
unnamed: IC1.7 (RG), R10.1, RGAIN2.1
unnamed: IC1.6 (-IN), R8.2
unnamed: IC1.5 (+IN), R7.2
unnamed: REF_LDO.1, U$1.AREF
unnamed: CH2.1, CHP2B.1, X1.4
unnamed: CH2.2, CHP2A.1, X1.3
unnamed: S1_A11.1, U$1.A11
unnamed: CHP1B.2, R1.2, R5.1
unnamed: CHP1A.2, R2.1, R6.1
unnamed: S1_A6.1, U$1.20/A6
unnamed: S1_A7.1, U$1.21/A7
unnamed: IC1.13 (OUT), R9.2, R11.1
unnamed: IC2.2 (-IN_A), R13.1, R15.1
unnamed: S2_A5.1, U$1.19/A5/SCL
unnamed: C7.1, IC2.3 (+IN_A), RTP1.2
unnamed: S2_A4.1, U$1.18/A4/SDA
unnamed: S2_A3.1, U$1.17/A3
unnamed: S2_A2.1, U$1.16/A2
unnamed: 3V3.1, U$1.3V3_LO
unnamed: CHP2B.2, R4.2, R8.1
unnamed: CHP2A.2, R3.1, R7.1
unnamed: C5.1, R12.2, RTP2.2
unnamed: IC1.9 (OUT), R10.2, R12.1
unnamed: C8.1, IC2.5 (+IN_B), RTP2.1
unnamed: IC2.6 (-IN_B), R14.1, R16.1
SIGNAL1: C5.2, IC2.7 (OUT_B), R14.2, S1_A6.2, S1_A7.2, S1_A10.2, S1_A11.2
SIGNAL2: C4.2, IC2.1 (OUTA), R13.2, S2_A2.2, S2_A3.2, S2_A4.2, S2_A5.2
VDD: 3V3.2, C1.1, C2.2, C6.2, C9.2, C10.1, IC1.8 (SHUTDOWN), IC1.11 (V+), IC1.14 (SHUTDOWN), IC2.8 (V+), IC3.5 (OUT), REF_LDO.2, VREF.3 (EN), VREF.4 (VIN)
VREF: C3.2, C7.2, C8.2, IC1.10 (REF), IC1.12 (REF), R1.1, R2.2, R3.2, R4.1, R15.2, R16.2, RGAIN1.1, RGAIN2.2, VREF.5 (VOUT_S), VREF.6 (VOUT_F)

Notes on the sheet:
High pass filter Pos 1: 10 Hz Pos 2: 100 Hz Pos 3: 300 Hz
Gain (ca.): Pos. 1: 5x Pos. 2: 30x Pos. 3: 180x
Low pass filter: Pos. 1: 7 kHz Pos. 2: 14 kHz Pos. 3: 30 kHz
Flood decoupling capacitors
Teensy Analog Amp
v 1.0
Last update: 2021/06/14
Two stage instrumentation amplifier
LDO: ADC Reference Votlage 1.2V

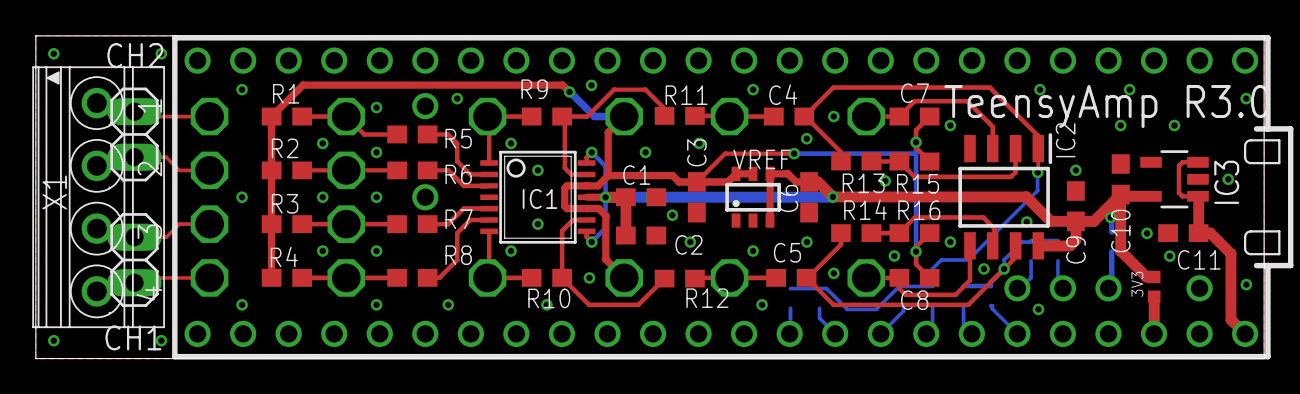
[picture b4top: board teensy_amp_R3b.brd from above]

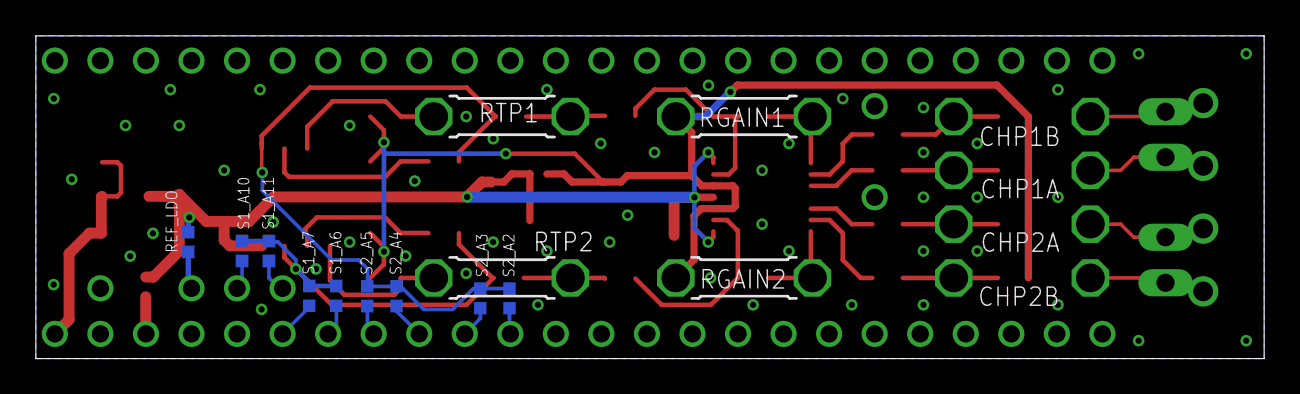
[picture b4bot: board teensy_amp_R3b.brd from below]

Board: 2 copper layers, 68.5 x 18.0 mm, 53 parts (17 on the bottom side), 38 nets.
